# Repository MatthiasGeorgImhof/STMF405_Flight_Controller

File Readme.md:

A flight controller inspired by Speedybee F405 v3 but with CAN and flash memory instead of flash card.

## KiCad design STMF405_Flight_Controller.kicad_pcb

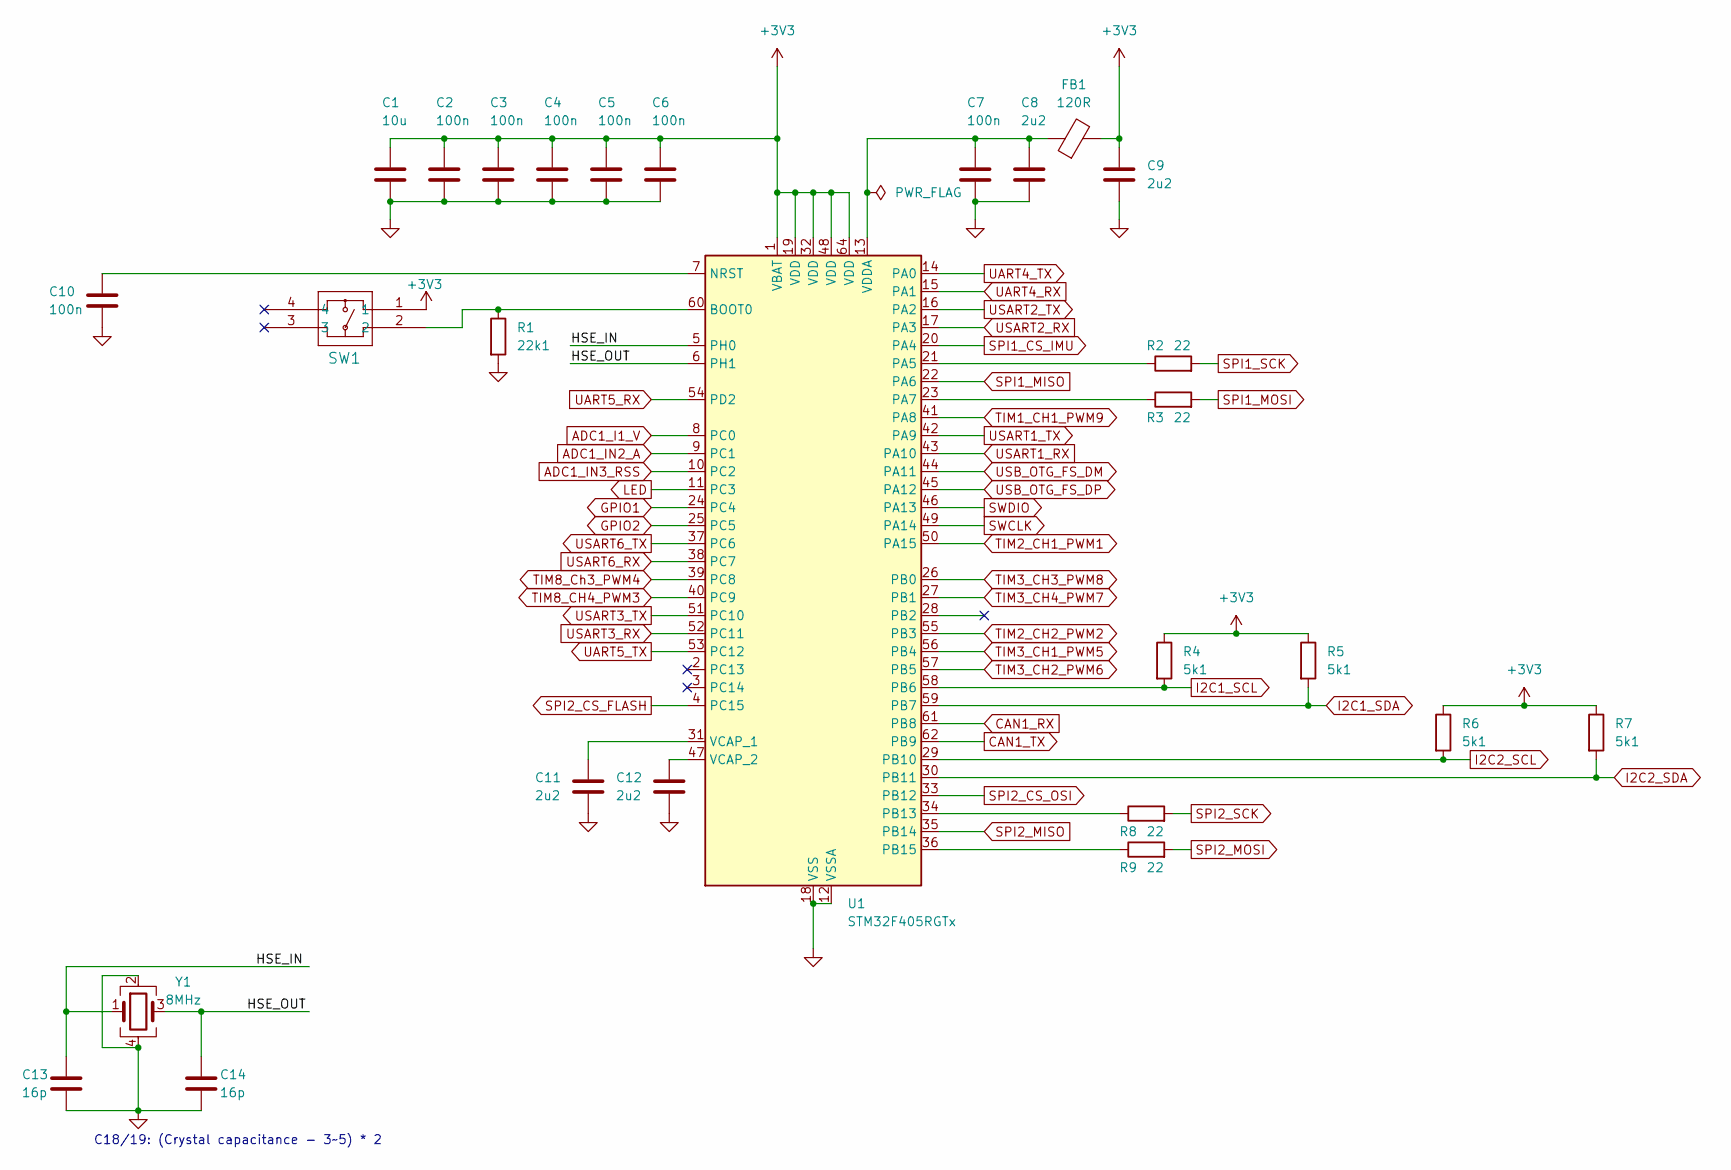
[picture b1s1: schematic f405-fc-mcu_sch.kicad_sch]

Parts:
C1: 10u; C_0805_2012Metric; Voltage 50; Tolerance 10%; Part Number GRM21BR61H106KE43K
C2, C3, C4, C5, C6, C7, C10: 100n; C_0201_0603Metric; Voltage 25; Tolerance 10%; Part Number GRM033R61E104KE14J
C8, C9, C11, C12: 2u2; C_0402_1005Metric; Voltage 25; Tolerance 10%; Part Number GRT155R61E225KE13D
C13, C14: 16p; C_0402_1005Metric; Voltage 50; Tolerance 1%; Part Number GCM1555C1H160FA16D
FB1: 120R; L_0603_1608Metric; Voltage 2.5; Part Number MI0603M121R-10
R1: 22k1; R_0201_0603Metric; Tolerance 1%; Part Number RC0201FR-0722K1L
R2, R3, R8, R9: 22; R_0201_0603Metric; Tolerance 1%; Part Number RC0201FR-0722RL
R4, R5, R6, R7: 5k1; R_0201_0603Metric; Tolerance 1%; Part Number RC0201FR-075K1L
SW1: EVP-AA602W; EVPAA&slash_EVP2A_PAN; Part Number EVP-AA602W
U1: STM32F405RGTx; LQFP-64_10x10mm_P0.5mm; Part Number STM32F405RGT6
Y1: 8MHz; Crystal_SMD_3225-4Pin_3.2x2.5mm; Part Number ECS-80-12-33-JGN-TR

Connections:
+3V3: C1.1, C2.1, C3.1, C4.1, C5.1, C6.1, C9.1, FB1.2, R4.1, R5.1, R6.1, R7.1, SW1.1, U1.1 (VBAT), U1.19 (VDD), U1.32 (VDD), U1.48 (VDD), U1.64 (VDD); also elsewhere on the board
/MCU/HSE_IN: C13.1, U1.5 (PH0), Y1.1
/MCU/HSE_OUT: C14.1, U1.6 (PH1), Y1.3
ADC1_I1_V: U1.8 (PC0); also elsewhere on the board
ADC1_IN2_A: U1.9 (PC1); also elsewhere on the board
ADC1_IN3_RSS: U1.10 (PC2); also elsewhere on the board
CAN1_RX: U1.61 (PB8); also elsewhere on the board
CAN1_TX: U1.62 (PB9); also elsewhere on the board
GND: C1.2, C2.2, C3.2, C4.2, C5.2, C6.2, C7.2, C8.2, C9.2, C10.2, C11.2, C12.2, C13.2, C14.2, R1.2, U1.12 (VSSA), U1.18 (VSS), U1.63 (VSS), Y1.2, Y1.4; also elsewhere on the board
GPIO1: U1.24 (PC4); also elsewhere on the board
GPIO2: U1.25 (PC5); also elsewhere on the board
I2C1_SCL: R4.2, U1.58 (PB6); also elsewhere on the board
I2C1_SDA: R5.2, U1.59 (PB7); also elsewhere on the board
I2C2_SCL: R6.2, U1.29 (PB10); also elsewhere on the board
I2C2_SDA: R7.2, U1.30 (PB11); also elsewhere on the board
LED: U1.11 (PC3); also elsewhere on the board
unnamed: R1.1, SW1.2, U1.60 (BOOT0)
unnamed: C10.1, U1.7 (NRST)
unnamed: R2.1, U1.21 (PA5)
unnamed: R3.1, U1.23 (PA7)
unnamed: R8.1, U1.34 (PB13)
unnamed: R9.1, U1.36 (PB15)
unnamed: C11.1, U1.31 (VCAP_1)
unnamed: C12.1, U1.47 (VCAP_2)
unnamed: C7.1, C8.1, FB1.1, U1.13 (VDDA)
SPI1_CS_IMU: U1.20 (PA4); also elsewhere on the board
SPI1_MISO: U1.22 (PA6); also elsewhere on the board
SPI1_MOSI: R3.2; also elsewhere on the board
SPI1_SCK: R2.2; also elsewhere on the board
SPI2_CS_FLASH: U1.4 (PC15); also elsewhere on the board
SPI2_CS_OSI: U1.33 (PB12); also elsewhere on the board
SPI2_MISO: U1.35 (PB14); also elsewhere on the board
SPI2_MOSI: R9.2; also elsewhere on the board
SPI2_SCK: R8.2; also elsewhere on the board
SWCLK: U1.49 (PA14); also elsewhere on the board
SWDIO: U1.46 (PA13); also elsewhere on the board
TIM1_CH1_PWM9: U1.41 (PA8); also elsewhere on the board
TIM2_CH1_PWM1: U1.50 (PA15); also elsewhere on the board
TIM2_CH2_PWM2: U1.55 (PB3); also elsewhere on the board
TIM3_CH1_PWM5: U1.56 (PB4); also elsewhere on the board
TIM3_CH2_PWM6: U1.57 (PB5); also elsewhere on the board
TIM3_CH3_PWM8: U1.26 (PB0); also elsewhere on the board
TIM3_CH4_PWM7: U1.27 (PB1); also elsewhere on the board
TIM8_CH4_PWM3: U1.40 (PC9); also elsewhere on the board
TIM8_Ch3_PWM4: U1.39 (PC8); also elsewhere on the board
UART4_RX: U1.15 (PA1); also elsewhere on the board
UART4_TX: U1.14 (PA0); also elsewhere on the board
UART5_RX: U1.54 (PD2); also elsewhere on the board
UART5_TX: U1.53 (PC12); also elsewhere on the board
USART1_RX: U1.43 (PA10); also elsewhere on the board
USART1_TX: U1.42 (PA9); also elsewhere on the board
USART2_RX: U1.17 (PA3); also elsewhere on the board
USART2_TX: U1.16 (PA2); also elsewhere on the board
USART3_RX: U1.52 (PC11); also elsewhere on the board
USART3_TX: U1.51 (PC10); also elsewhere on the board
USART6_RX: U1.38 (PC7); also elsewhere on the board
USART6_TX: U1.37 (PC6); also elsewhere on the board
USB_OTG_FS_DM: U1.44 (PA11); also elsewhere on the board
USB_OTG_FS_DP: U1.45 (PA12); also elsewhere on the board

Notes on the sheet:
C18/19: (Crystal capacitance - 3~5) * 2

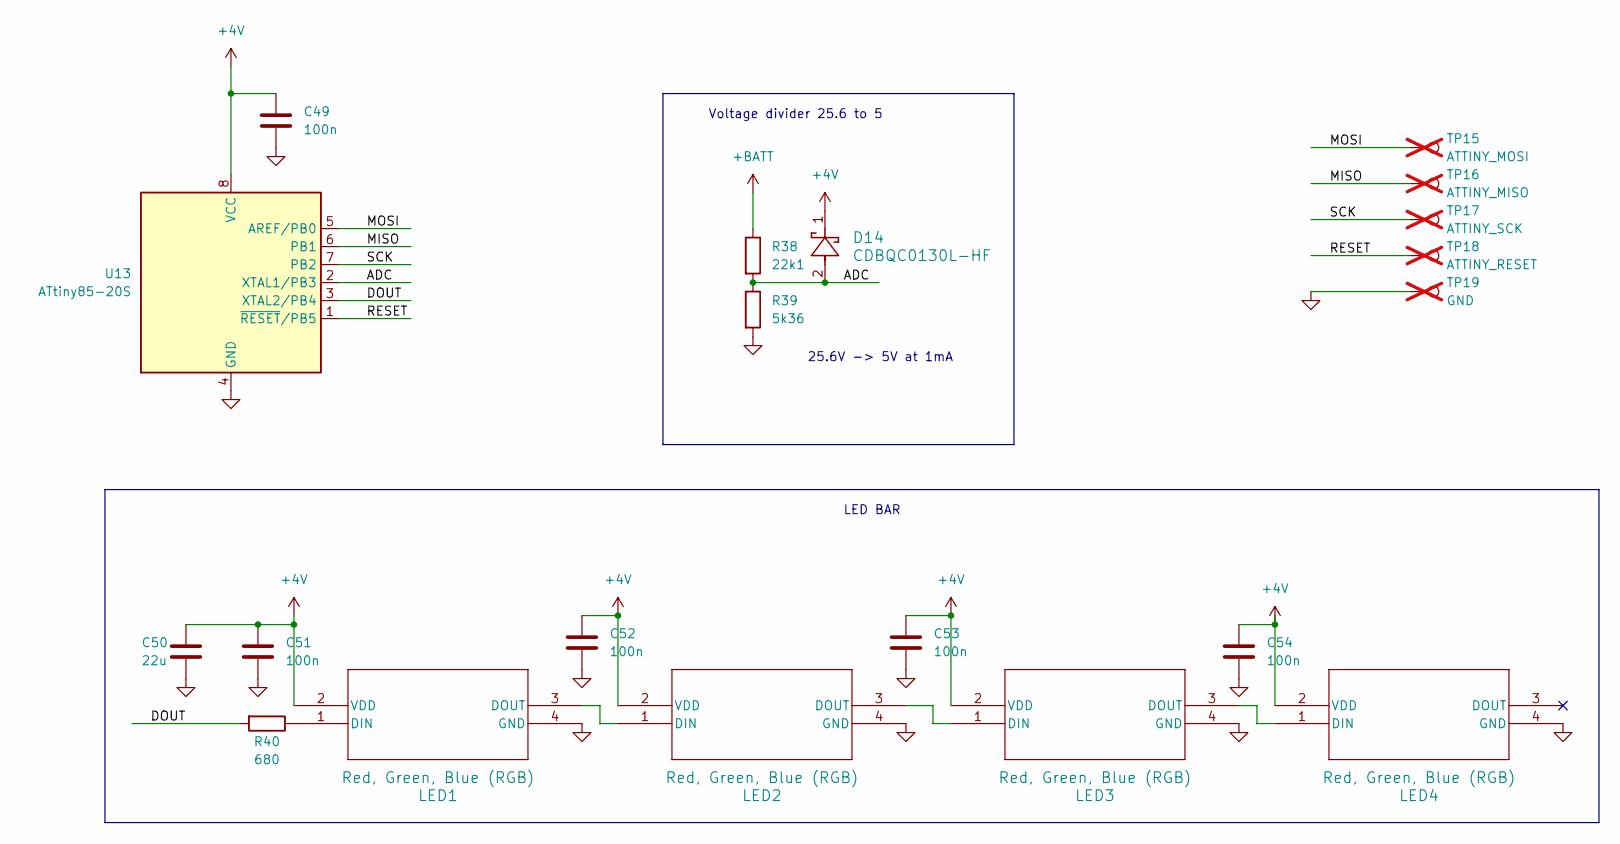
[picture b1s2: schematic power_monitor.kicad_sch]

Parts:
C49, C51, C53, C54: 100n; C_0201_0603Metric; Voltage 25; Tolerance 10%; Part Number GRM033R61E104KE14J
C50: 22u; C_0805_2012Metric; Tolerance 20%; Voltage 25; Part Number GRM21BR61E226ME44K
C52: 100n; C_0201_0603Metric; Tolerance 10%; Voltage 25; Part Number GRM033R61E104KE14J
D14: CDBQC0130L-HF; SDO_0402C&slash_SOD-923F_CIP; Voltage 30; Part Number CDBQC0130L-HF
LED1, LED2, LED3, LED4: Red, Green, Blue (RGB); IN-PI15_INL; Part Number IN-PI15TAT5R5G5B
R38: 22k1; R_0201_0603Metric; Tolerance 1%; Part Number RC0201FR-0722K1L
R39: 5k36; R_0201_0603Metric; Tolerance 1%; Part Number RC0201FR-075K36L
R40: 680; R_0201_0603Metric; Tolerance 1%; Part Number RC0201FR-07680RL
TP15: ATTINY_MOSI; TestPoint_Pad_1.0x1.5mm; not fitted
TP16: ATTINY_MISO; TestPoint_Pad_1.0x1.5mm; not fitted
TP17: ATTINY_SCK; TestPoint_Pad_1.0x1.5mm; not fitted
TP18: ATTINY_RESET; TestPoint_Pad_1.0x1.5mm; not fitted
TP19: GND; TestPoint_Pad_1.0x1.5mm; not fitted
U13: ATtiny85-20S; SOIC-8W_5.3x5.3mm_P1.27mm; Part Number ATTINY85-20SU

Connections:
+4V: C49.1, C50.1, C51.1, C52.1, C53.1, C54.1, D14.1, LED1.2 (VDD), LED2.2 (VDD), LED3.2 (VDD), LED4.2 (VDD), U13.8 (VCC); also elsewhere on the board
+BATT: R38.1; also elsewhere on the board
/Power Monitor/ADC: D14.2, R38.2, R39.1, U13.2 (XTAL1/PB3)
/Power Monitor/DOUT: R40.2, U13.3 (XTAL2/PB4)
/Power Monitor/MISO: TP16.1, U13.6 (PB1)
/Power Monitor/MOSI: TP15.1, U13.5 (AREF/PB0)
/Power Monitor/RESET: TP18.1, U13.1 (~RESET/PB5)
/Power Monitor/SCK: TP17.1, U13.7 (PB2)
GND: C49.2, C50.2, C51.2, C52.2, C53.2, C54.2, LED1.4 (GND), LED2.4 (GND), LED3.4 (GND), LED4.4 (GND), R39.2, TP19.1, U13.4 (GND); also elsewhere on the board
unnamed: LED1.1 (DIN), R40.1
unnamed: LED1.3 (DOUT), LED2.1 (DIN)
unnamed: LED2.3 (DOUT), LED3.1 (DIN)
unnamed: LED3.3 (DOUT), LED4.1 (DIN)

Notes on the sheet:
Voltage divider 25.6 to 5
LED BAR
25.6V -> 5V at 1mA

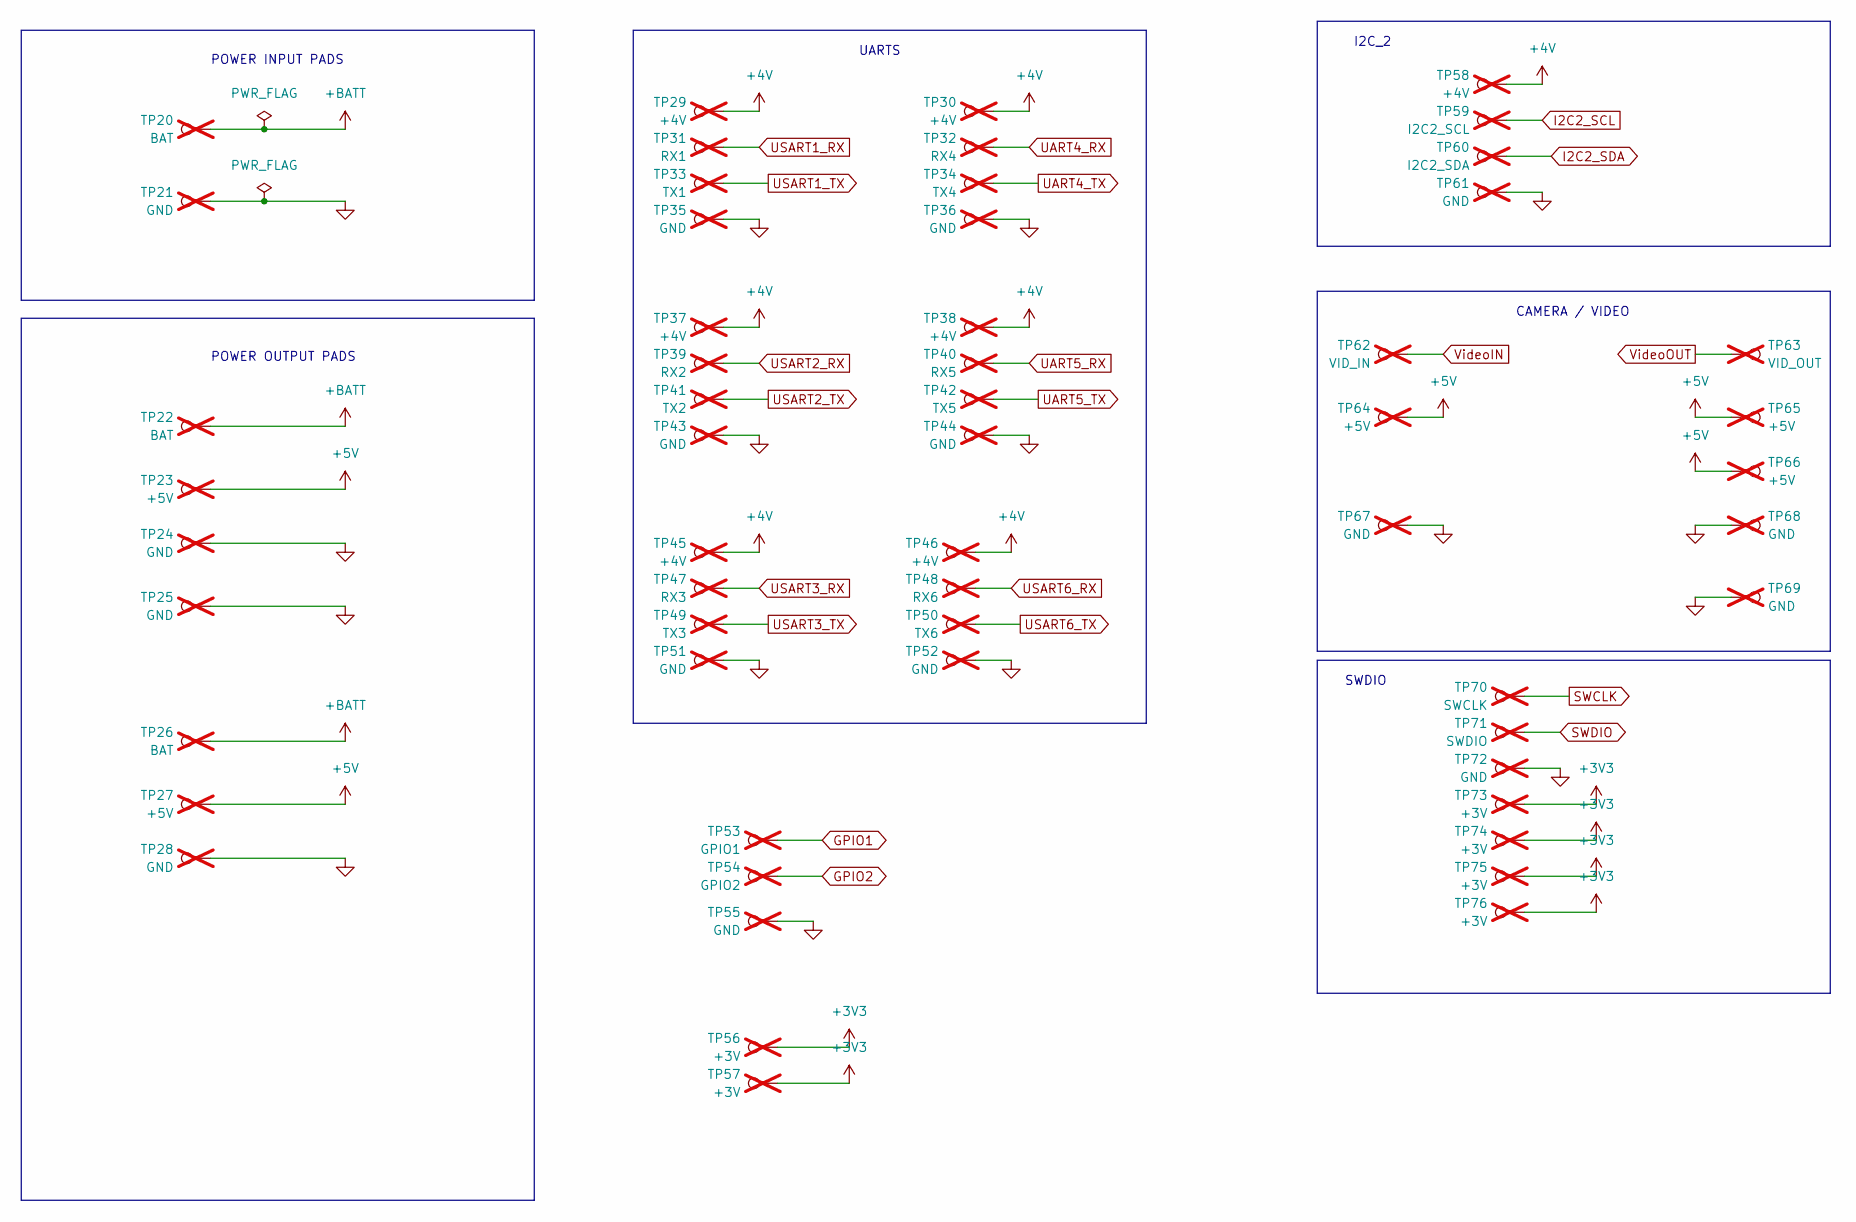
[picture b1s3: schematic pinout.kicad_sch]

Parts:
TP20: BAT; TestPoint_Pad_1.5x1.5mm; not fitted
TP21: GND; TestPoint_Pad_1.5x1.5mm; not fitted
TP22, TP26: BAT; TestPoint_Pad_1.0x1.5mm; not fitted
TP23, TP27, TP64, TP65, TP66: +5V; TestPoint_Pad_1.0x1.5mm; not fitted
TP24, TP25, TP28, TP35, TP36, TP43, TP44, TP51, TP52, TP55, TP61, TP67, TP68, TP69, TP72: GND; TestPoint_Pad_1.0x1.5mm; not fitted
TP29, TP30, TP37, TP38, TP45, TP46, TP58: +4V; TestPoint_Pad_1.0x1.5mm; not fitted
TP31: RX1; TestPoint_Pad_1.0x1.5mm; not fitted
TP32: RX4; TestPoint_Pad_1.0x1.5mm; not fitted
TP33: TX1; TestPoint_Pad_1.0x1.5mm; not fitted
TP34: TX4; TestPoint_Pad_1.0x1.5mm; not fitted
TP39: RX2; TestPoint_Pad_1.0x1.5mm; not fitted
TP40: RX5; TestPoint_Pad_1.0x1.5mm; not fitted
TP41: TX2; TestPoint_Pad_1.0x1.5mm; not fitted
TP42: TX5; TestPoint_Pad_1.0x1.5mm; not fitted
TP47: RX3; TestPoint_Pad_1.0x1.5mm; not fitted
TP48: RX6; TestPoint_Pad_1.0x1.5mm; not fitted
TP49: TX3; TestPoint_Pad_1.0x1.5mm; not fitted
TP50: TX6; TestPoint_Pad_1.0x1.5mm; not fitted
TP53: GPIO1; TestPoint_Pad_1.0x1.5mm; not fitted
TP54: GPIO2; TestPoint_Pad_1.0x1.5mm; not fitted
TP56, TP57, TP73, TP74, TP75, TP76: +3V; TestPoint_Pad_1.0x1.5mm; not fitted
TP59: I2C2_SCL; TestPoint_Pad_1.0x1.5mm; not fitted
TP60: I2C2_SDA; TestPoint_Pad_1.0x1.5mm; not fitted
TP62: VID_IN; TestPoint_Pad_1.0x1.5mm; not fitted
TP63: VID_OUT; TestPoint_Pad_1.0x1.5mm; not fitted
TP70: SWCLK; TestPoint_Pad_1.0x1.5mm; not fitted
TP71: SWDIO; TestPoint_Pad_1.0x1.5mm; not fitted

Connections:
+3V3: TP56.1, TP57.1, TP73.1, TP74.1, TP75.1, TP76.1; also elsewhere on the board
+4V: TP29.1, TP30.1, TP37.1, TP38.1, TP45.1, TP46.1, TP58.1; also elsewhere on the board
+5V: TP23.1, TP27.1, TP64.1, TP65.1, TP66.1; also elsewhere on the board
+BATT: TP20.1, TP22.1, TP26.1; also elsewhere on the board
GND: TP21.1, TP24.1, TP25.1, TP28.1, TP35.1, TP36.1, TP43.1, TP44.1, TP51.1, TP52.1, TP55.1, TP61.1, TP67.1, TP68.1, TP69.1, TP72.1; also elsewhere on the board
GPIO1: TP53.1; also elsewhere on the board
GPIO2: TP54.1; also elsewhere on the board
I2C2_SCL: TP59.1; also elsewhere on the board
I2C2_SDA: TP60.1; also elsewhere on the board
SWCLK: TP70.1; also elsewhere on the board
SWDIO: TP71.1; also elsewhere on the board
UART4_RX: TP32.1; also elsewhere on the board
UART4_TX: TP34.1; also elsewhere on the board
UART5_RX: TP40.1; also elsewhere on the board
UART5_TX: TP42.1; also elsewhere on the board
USART1_RX: TP31.1; also elsewhere on the board
USART1_TX: TP33.1; also elsewhere on the board
USART2_RX: TP39.1; also elsewhere on the board
USART2_TX: TP41.1; also elsewhere on the board
USART3_RX: TP47.1; also elsewhere on the board
USART3_TX: TP49.1; also elsewhere on the board
USART6_RX: TP48.1; also elsewhere on the board
USART6_TX: TP50.1; also elsewhere on the board
VideoIN: TP62.1; also elsewhere on the board
VideoOUT: TP63.1; also elsewhere on the board

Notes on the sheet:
I2C_2
POWER OUTPUT PADS
UARTS
CAMERA / VIDEO
POWER INPUT PADS
SWDIO

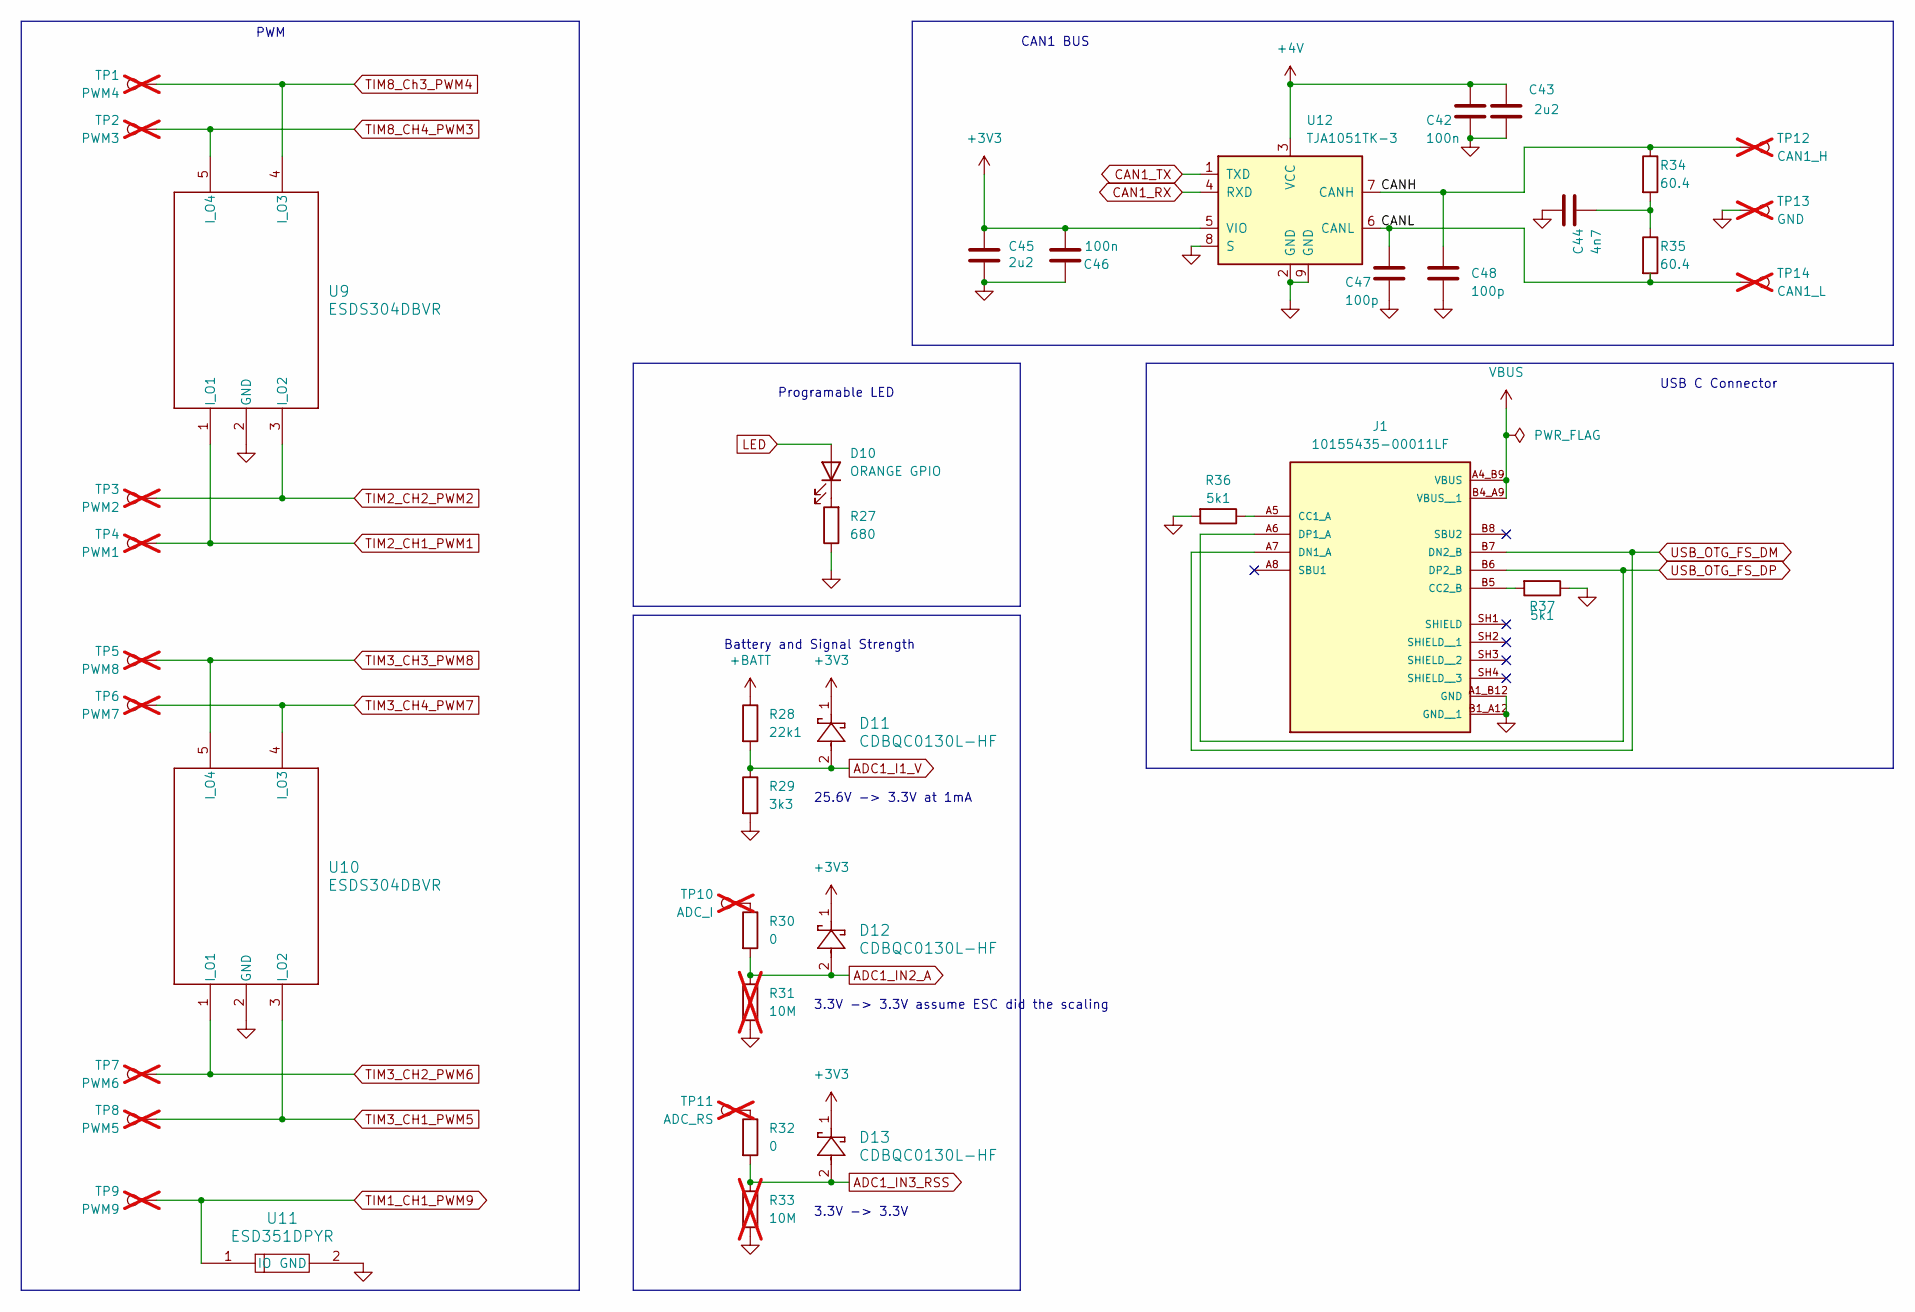
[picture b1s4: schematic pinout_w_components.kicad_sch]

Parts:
C42, C46: 100n; C_0201_0603Metric; Voltage 25; Tolerance 10%; Part Number GRM033R61E104KE14J
C43, C45: 2u2; C_0402_1005Metric; Voltage 25; Tolerance 10%; Part Number GRT155R61E225KE13D
C44: 4n7; C_0402_1005Metric; Voltage 50; Tolerance 10%; Part Number GRM155R61H472KA01D
C47, C48: 100p; C_0402_1005Metric; Voltage 50; Tolerance 5%; Part Number GRM1555C1H101JA01D
D10: ORANGE GPIO; LED_0603_1608Metric; Voltage 2; Part Number LTST-C191KFKT
D11, D12, D13: CDBQC0130L-HF; SDO_0402C&slash_SOD-923F_CIP; Voltage 30; Part Number CDBQC0130L-HF
J1: 10155435-00011LF; AMPHENOL_10155435-00011LF; Part Number 10155435-00011LF
R27: 680; R_0201_0603Metric; Tolerance 1%; Part Number RC0201FR-07680RL
R28: 22k1; R_0201_0603Metric; Tolerance 1%; Part Number RC0201FR-0722K1L
R29: 3k3; R_0201_0603Metric; Tolerance 1%; Part Number RC0201FR-073K3L
R30, R32: 0; R_0201_0603Metric; Part Number RC0201FR-070RL
R31, R33: 10M; R_0201_0603Metric; Tolerance 1%; Part Number RC0201FR-0710ML; not fitted
R34, R35: 60.4; R_0201_0603Metric; Tolerance 1%; Part Number RC0201FR-0760R4L
R36, R37: 5k1; R_0201_0603Metric; Tolerance 1%; Part Number RC0201FR-075K1L
TP1: PWM4; TestPoint_Pad_1.0x1.5mm; not fitted
TP2: PWM3; TestPoint_Pad_1.0x1.5mm; not fitted
TP3: PWM2; TestPoint_Pad_1.0x1.5mm; not fitted
TP4: PWM1; TestPoint_Pad_1.0x1.5mm; not fitted
TP5: PWM8; TestPoint_Pad_1.0x1.5mm; not fitted
TP6: PWM7; TestPoint_Pad_1.0x1.5mm; not fitted
TP7: PWM6; TestPoint_Pad_1.0x1.5mm; not fitted
TP8: PWM5; TestPoint_Pad_1.0x1.5mm; not fitted
TP9: PWM9; TestPoint_Pad_1.0x1.5mm; not fitted
TP10: ADC_I; TestPoint_Pad_1.0x1.5mm; not fitted
TP11: ADC_RS; TestPoint_Pad_1.0x1.5mm; not fitted
TP12: CAN1_H; TestPoint_Pad_1.0x1.5mm; not fitted
TP13: GND; TestPoint_Pad_1.0x1.5mm; not fitted
TP14: CAN1_L; TestPoint_Pad_1.0x1.5mm; not fitted
U9, U10: ESDS304DBVR; DBV0005A_L; Part Number ESDS304DBVR
U11: ESD351DPYR; DPY2_TEX; Part Number ESD351DPYR
U12: TJA1051TK-3; DFN-8-1EP_3x3mm_P0.65mm_EP1.55x2.4mm; Part Number TJA1051TK/3,118

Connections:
+3V3: C45.1, C46.2, D11.1, D12.1, D13.1, U12.5 (VIO); also elsewhere on the board
+4V: C42.1, C43.1, U12.3 (VCC); also elsewhere on the board
+BATT: R28.1; also elsewhere on the board
/Pinout with components/CANH: C48.1, R34.1, TP12.1, U12.7 (CANH)
/Pinout with components/CANL: C47.1, R35.2, TP14.1, U12.6 (CANL)
ADC1_I1_V: D11.2, R28.2, R29.1; also elsewhere on the board
ADC1_IN2_A: D12.2, R30.2, R31.1; also elsewhere on the board
ADC1_IN3_RSS: D13.2, R32.2, R33.1; also elsewhere on the board
CAN1_RX: U12.4 (RXD); also elsewhere on the board
CAN1_TX: U12.1 (TXD); also elsewhere on the board
GND: C42.2, C43.2, C44.1, C45.2, C46.1, C47.2, C48.2, J1.A1_B12 (GND), J1.B1_A12 (GND__1), R27.1, R29.2, R31.2, R33.2, R36.2, R37.1, TP13.1, U9.2 (GND), U10.2 (GND), U11.2 (GND), U12.2 (GND), U12.8 (S), U12.9 (GND); also elsewhere on the board
LED: D10.2 (A); also elsewhere on the board
unnamed: C44.2, R34.2, R35.1
unnamed: D10.1 (K), R27.2
unnamed: J1.A5 (CC1_A), R36.1
unnamed: J1.B5 (CC2_B), R37.2
unnamed: R30.1, TP10.1
unnamed: R32.1, TP11.1
TIM1_CH1_PWM9: TP9.1, U11.1 (IO); also elsewhere on the board
TIM2_CH1_PWM1: TP4.1, U9.1 (I_O1); also elsewhere on the board
TIM2_CH2_PWM2: TP3.1, U9.3 (I_O2); also elsewhere on the board
TIM3_CH1_PWM5: TP8.1, U10.3 (I_O2); also elsewhere on the board
TIM3_CH2_PWM6: TP7.1, U10.1 (I_O1); also elsewhere on the board
TIM3_CH3_PWM8: TP5.1, U10.5 (I_O4); also elsewhere on the board
TIM3_CH4_PWM7: TP6.1, U10.4 (I_O3); also elsewhere on the board
TIM8_CH4_PWM3: TP2.1, U9.5 (I_O4); also elsewhere on the board
TIM8_Ch3_PWM4: TP1.1, U9.4 (I_O3); also elsewhere on the board
USB_OTG_FS_DM: J1.A7 (DN1_A), J1.B7 (DN2_B); also elsewhere on the board
USB_OTG_FS_DP: J1.A6 (DP1_A), J1.B6 (DP2_B); also elsewhere on the board
VBUS: J1.A4_B9 (VBUS), J1.B4_A9 (VBUS__1); also elsewhere on the board

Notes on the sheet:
3.3V -> 3.3V assume ESC did the scaling
Battery and Signal Strength
25.6V -> 3.3V at 1mA
Programable LED
CAN1 BUS
PWM
USB C Connector
3.3V -> 3.3V

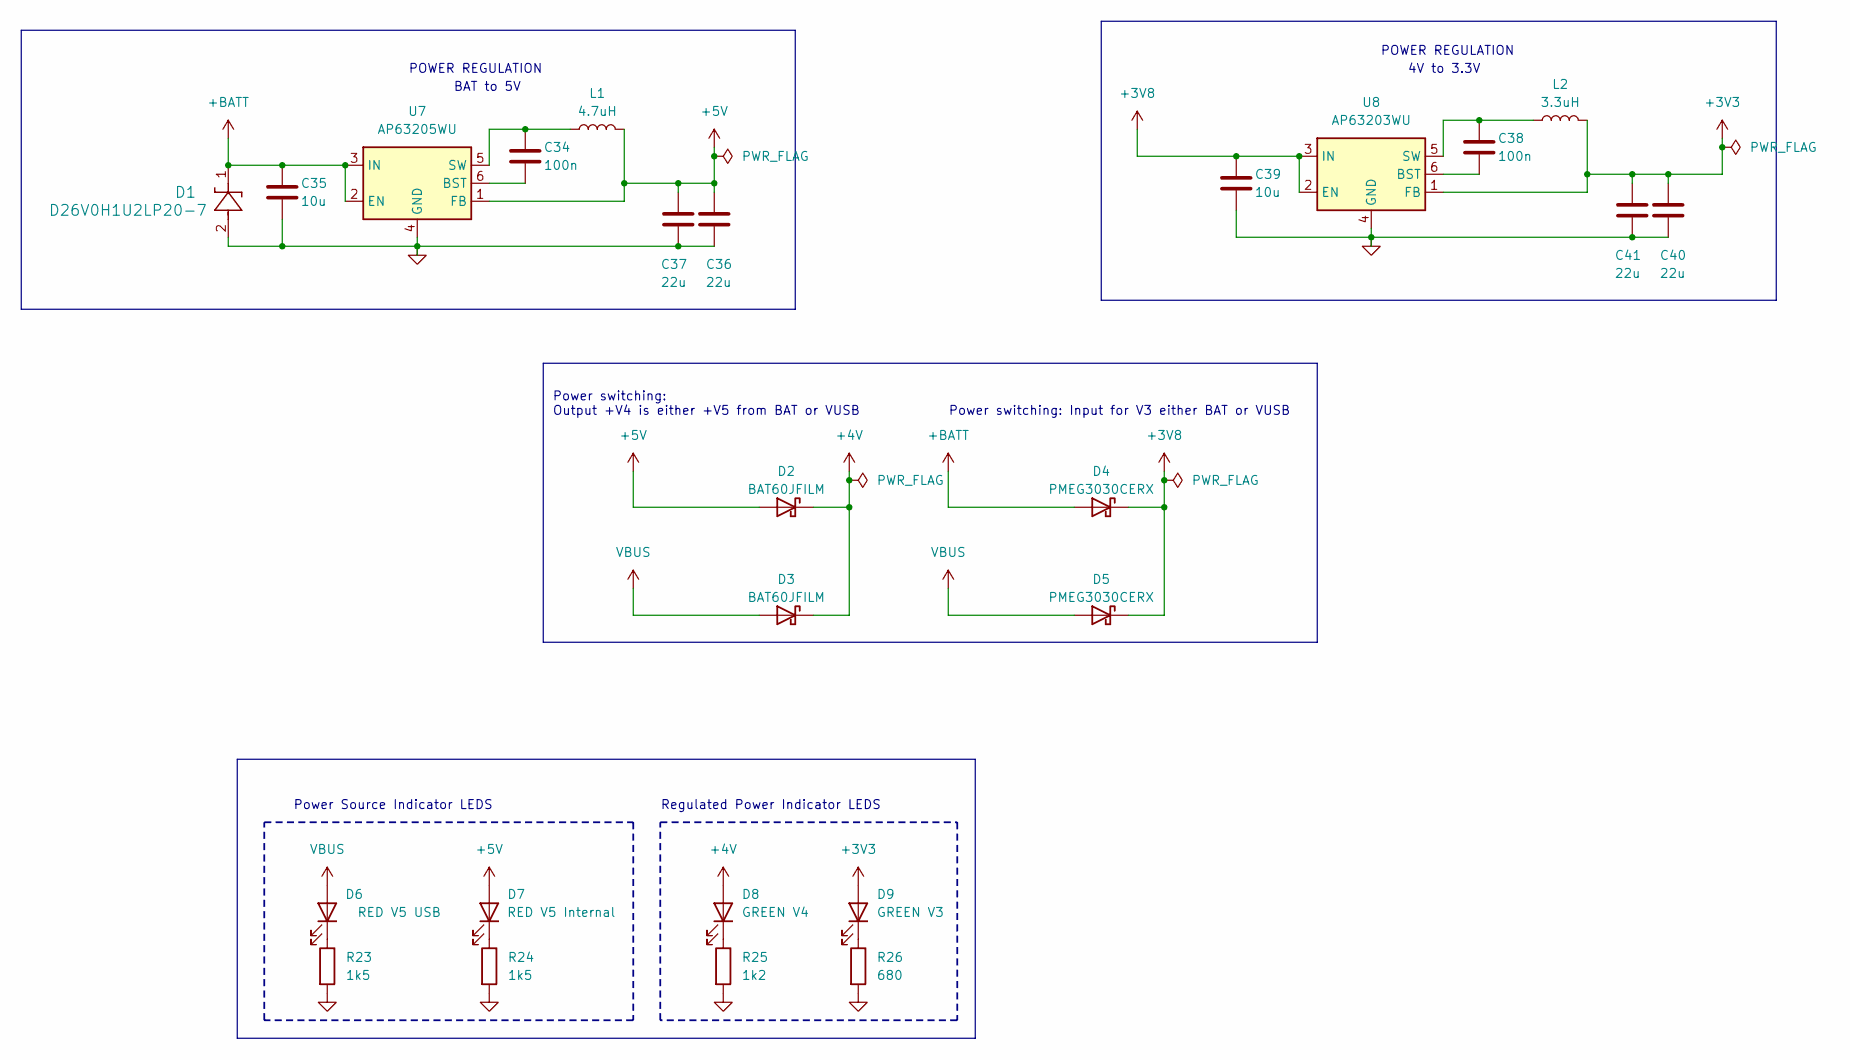
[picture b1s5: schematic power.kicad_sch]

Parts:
C34, C38: 100n; C_0201_0603Metric; Voltage 25; Tolerance 10%; Part Number GRM033R61E104KE14J
C35, C39: 10u; C_0805_2012Metric; Voltage 50; Tolerance 10%; Part Number GRM21BR61H106KE43K
C36, C37, C40, C41: 22u; C_0805_2012Metric; Voltage 25; Tolerance 20%; Part Number GRM21BR61E226ME44K
D1: D26V0H1U2LP20-7; U-DFN2020-2_DIO-L; Voltage 26; Part Number D26V0H1U2LP20-7
D2, D3: BAT60JFILM; D_SOD-323; Voltage 10; Part Number BAT60JFILM
D4, D5: PMEG3030CERX; Nexperia_CFP3_SOD-123W; Voltage 30; Part Number PMEG3030CERX
D6: RED V5 USB; LED_0603_1608Metric; Voltage 2; Part Number LTST-C191KRKT
D7: RED V5 Internal; LED_0603_1608Metric; Voltage 2; Part Number LTST-C191KRKT
D8: GREEN V4; LED_0603_1608Metric; Voltage 2.1; Part Number LTST-C191GKT
D9: GREEN V3; LED_0603_1608Metric; Voltage 2.1; Part Number LTST-C191GKT
L1: 4.7uH; L_1210_3225Metric; Tolerance 20%; Part Number DFE322520FD-4R7M=P2
L2: 3.3uH; L_1210_3225Metric; Tolerance 20%; Part Number DFE322512F-3R3M=P2
R23, R24: 1k5; R_0201_0603Metric; Tolerance 1%; Part Number RC0201FR-071K5L
R25: 1k2; R_0201_0603Metric; Tolerance 1%; Part Number RC0201FR-071K2L
R26: 680; R_0201_0603Metric; Tolerance 1%; Part Number RC0201FR-07680RL
U7: AP63205WU; TSOT-23-6; Voltage 5; Part Number AP63205WU-7
U8: AP63203WU; TSOT-23-6; Voltage 3; Part Number AP63203WU-7

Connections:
+3V3: C40.1, C41.1, D9.2 (A), L2.2, U8.1 (FB); also elsewhere on the board
+3V8: C39.1, D4.1 (K), D5.1 (K), U8.2 (EN), U8.3 (IN)
+4V: D2.1 (K), D3.1 (K), D8.2 (A); also elsewhere on the board
+5V: C36.1, C37.1, D2.2 (A), D7.2 (A), L1.2, U7.1 (FB); also elsewhere on the board
+BATT: C35.1, D1.1, D4.2 (A), U7.2 (EN), U7.3 (IN); also elsewhere on the board
GND: C35.2, C36.2, C37.2, C39.2, C40.2, C41.2, D1.2, R23.2, R24.2, R25.2, R26.2, U7.4 (GND), U8.4 (GND); also elsewhere on the board
unnamed: D6.1 (K), R23.1
unnamed: D7.1 (K), R24.1
unnamed: D8.1 (K), R25.1
unnamed: D9.1 (K), R26.1
unnamed: C34.2, U7.6 (BST)
unnamed: C34.1, L1.1, U7.5 (SW)
unnamed: C38.2, U8.6 (BST)
unnamed: C38.1, L2.1, U8.5 (SW)
VBUS: D3.2 (A), D5.2 (A), D6.2 (A); also elsewhere on the board

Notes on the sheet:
Power switching: Output +V4 is either +V5 from BAT or VUSB
BAT to 5V
Power switching: Input for V3 either BAT or VUSB
POWER REGULATION
Power Source Indicator LEDS
4V to 3.3V
Regulated Power Indicator LEDS

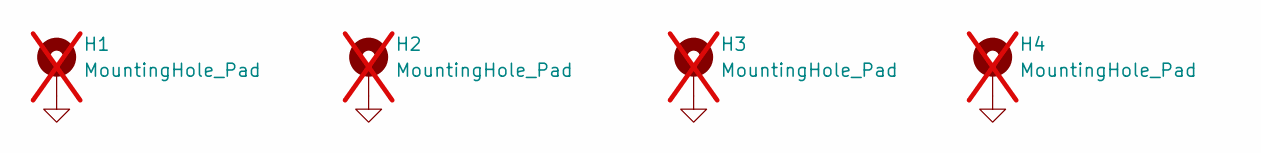
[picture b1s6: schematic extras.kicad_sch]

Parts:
H1, H2, H3, H4: MountingHole_Pad; MountingHole_4.3mm_M4_Pad_Via_Custom; not fitted

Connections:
GND: H1.1, H2.1, H3.1, H4.1; also elsewhere on the board
